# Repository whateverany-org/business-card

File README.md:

# business-card
My first ever PCB, a clone of https://www.thirtythreeforty.net/posts/2019/12/my-business-card-runs-linux. Completely untested, so not sure if it works or not. Build is waiting on on development of my reflow oven https://github.com/whateverany-org/reflow-oven.

# pcbdraw

## setup env
Create local env secrets and OCI container(s)
```
cp .env.template .env
vi .env
make oci-secrets
# rerun make oci-secrets if any changes to .env
make build
```

## create pcbdraw
```
make pcbdraw
```

### python venv hax
```
      
python3 -m venv .venv

```
rm -rf .venv/
python3 -m venv --system-site-packages .venv
source .venv/bin/activate
```

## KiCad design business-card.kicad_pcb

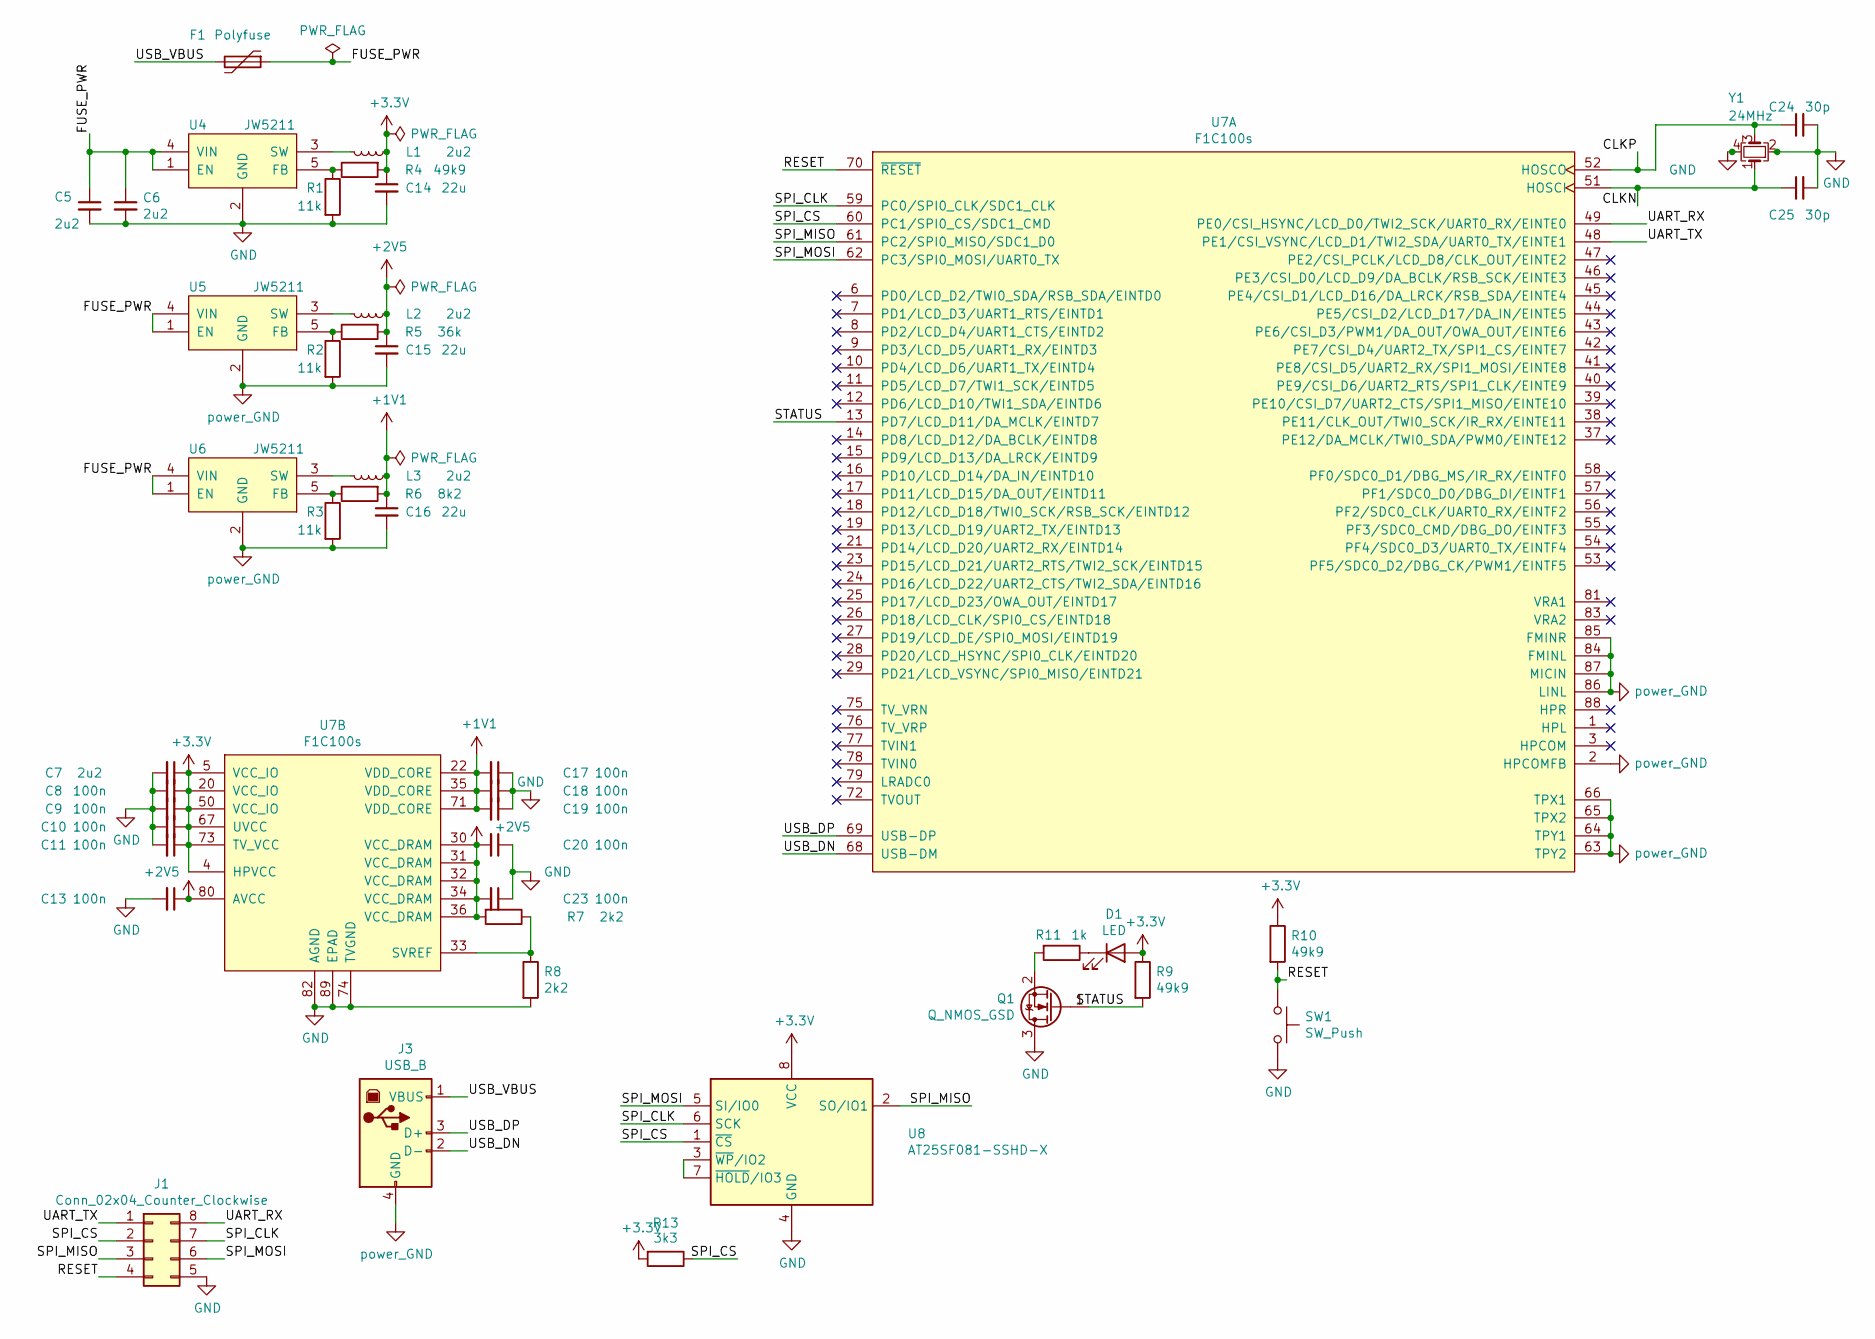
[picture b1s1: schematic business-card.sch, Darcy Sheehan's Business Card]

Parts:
C5, C6: 2u2; C_0805_2012Metric_Pad1.15x1.40mm_HandSolder
C7: 2u2; C_0805_2012Metric_Pad1.18x1.45mm_HandSolder
C8, C9, C10, C11, C13, C17, C18, C19, C20, C23: 100n; C_0805_2012Metric_Pad1.15x1.40mm_HandSolder
C14, C15, C16: 22u; C_0805_2012Metric_Pad1.15x1.40mm_HandSolder
C24, C25: 30p; C_0805_2012Metric_Pad1.15x1.40mm_HandSolder
D1: LED; LED_0805_2012Metric_Pad1.15x1.40mm_HandSolder
F1: Polyfuse; Fuse_0805_2012Metric
J1: Conn_02x04_Counter_Clockwise; SOIC_clipProgSmall
J3: USB_B; usb-PCB
L1, L2, L3: 2u2; L_0805_2012Metric_Pad1.15x1.40mm_HandSolder
Q1: Q_NMOS_GSD; SOT-23
R1, R2, R3: 11k; R_0805_2012Metric_Pad1.15x1.40mm_HandSolder
R4, R9, R10: 49k9; R_0805_2012Metric_Pad1.15x1.40mm_HandSolder
R5: 36k; R_0805_2012Metric_Pad1.15x1.40mm_HandSolder
R6: 8k2; R_0805_2012Metric_Pad1.15x1.40mm_HandSolder
R7, R8: 2k2; R_0805_2012Metric_Pad1.15x1.40mm_HandSolder
R11: 1k; R_0805_2012Metric_Pad1.15x1.40mm_HandSolder
R13: 3k3; R_0805_2012Metric_Pad1.15x1.40mm_HandSolder
SW1: SW_Push; SW_SPST_FSMSM
U4, U5, U6: JW5211; SOT-23-5
U7: F1C100s; QFN-88_EP_10x10_Pitch0.4mm
U8: AT25SF081-SSHD-X; SOIC-8_3.9x4.9mm_P1.27mm
Y1: 24MHz; Oscillator_SMD_Abracon_ASE-4Pin_3.2x2.5mm

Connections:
+1V1: C16.1, C17.2, C18.2, C19.2, L3.1, R6.2, U7.22 (VDD_CORE), U7.35 (VDD_CORE), U7.71 (VDD_CORE)
+2V5: C13.1, C15.1, C20.2, C23.2, L2.1, R5.2, R7.2, U7.30 (VCC_DRAM), U7.31 (VCC_DRAM), U7.32 (VCC_DRAM), U7.34 (VCC_DRAM), U7.36 (VCC_DRAM), U7.80 (AVCC)
+3V3: C7.1, C8.1, C9.1, C10.1, C11.1, C14.1, D1.2 (A), L1.1, R4.2, R9.1, R10.1, R13.2, U7.4 (HPVCC), U7.5 (VCC_IO), U7.20 (VCC_IO), U7.50 (VCC_IO), U7.67 (UVCC), U7.73 (TV_VCC), U8.8 (VCC)
/CLKN: C25.1, U7.51 (HOSCI), Y1.1
/CLKP: C24.1, U7.52 (HOSCO), Y1.3
/FUSE_PWR: C5.1, C6.1, F1.1, U4.1 (EN), U4.4 (VIN), U5.1 (EN), U5.4 (VIN), U6.1 (EN), U6.4 (VIN)
/RESET: J1.4, R10.2, SW1.1, U7.70 (~RESET)
/SPI_CLK: J1.7, U7.59 (PC0/SPI0_CLK/SDC1_CLK), U8.6 (SCK)
/SPI_CS: J1.2, R13.1, U7.60 (PC1/SPI0_CS/SDC1_CMD), U8.1 (~CS)
/SPI_MISO: J1.3, U7.61 (PC2/SPI0_MISO/SDC1_D0), U8.2 (SO/IO1)
/SPI_MOSI: J1.6, U7.62 (PC3/SPI0_MOSI/UART0_TX), U8.5 (SI/IO0)
/STATUS: Q1.1 (G), R9.2, U7.13 (PD7/LCD_D11/DA_MCLK/EINTD7)
/UART_RX: J1.8, U7.49 (PE0/CSI_HSYNC/LCD_D0/TWI2_SCK/UART0_RX/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)
/UART_TX: J1.1, U7.48 (PE1/CSI_VSYNC/LCD_D1/TWI2_SDA/UART0_TX/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)
/USB_DN: J3.2 (D-), U7.68 (USB-DM)
/USB_DP: J3.3 (D+), U7.69 (USB-DP)
/USB_VBUS: F1.2, J3.1 (VBUS)
unnamed: D1.1 (K), R11.1
unnamed: L1.2, U4.3 (SW)
unnamed: L2.2, U5.3 (SW)
unnamed: L3.2, U6.3 (SW)
unnamed: Q1.2 (S), R11.2
unnamed: R1.1, R4.1, U4.5 (FB)
unnamed: R2.1, R5.1, U5.5 (FB)
unnamed: R3.1, R6.1, U6.5 (FB)
unnamed: R7.1, R8.1, U7.33 (SVREF)
unnamed: U8.3 (~WP~/IO2), U8.7 (~HOLD~/IO3)

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
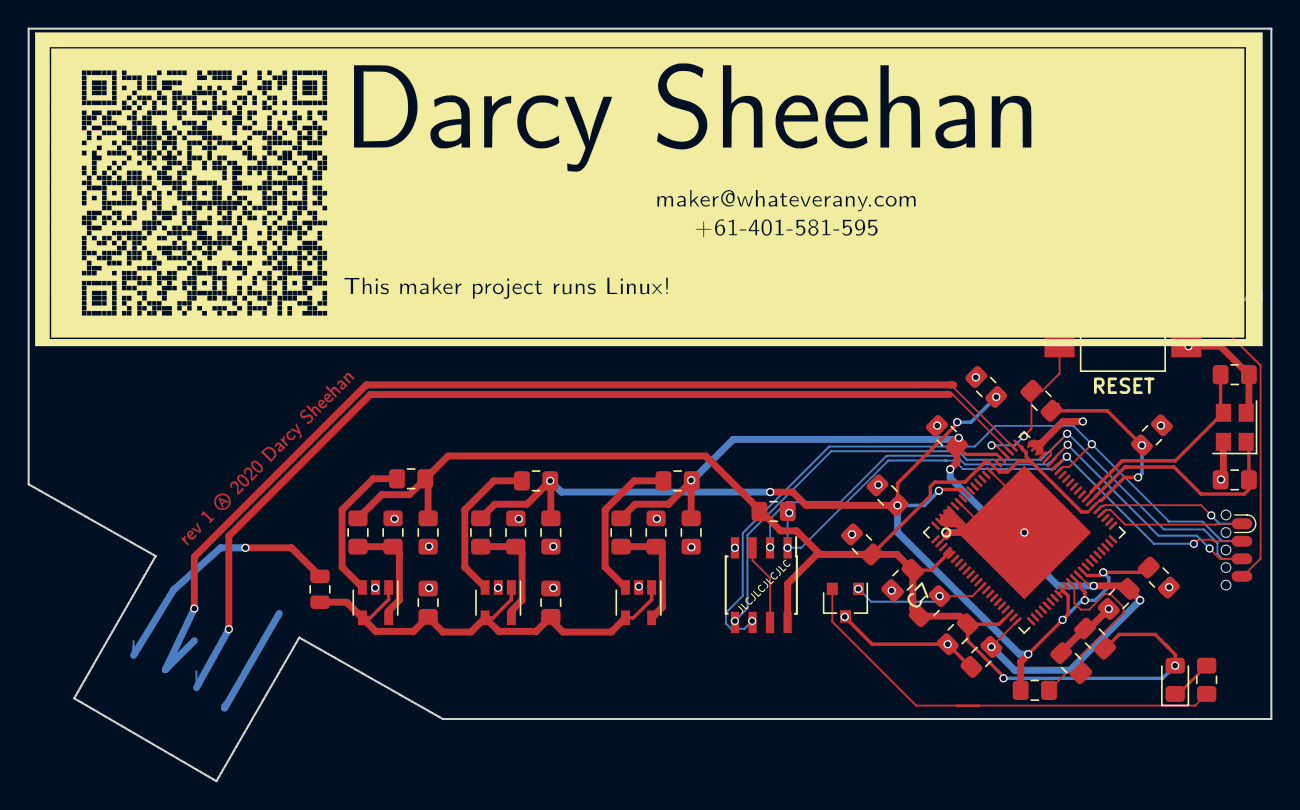
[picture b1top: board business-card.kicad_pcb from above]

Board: 2 copper layers, 90.0 x 54.5 mm, 45 parts (1 on the bottom side), 28 nets.

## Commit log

2020-11-29 stage 1
2020-11-30 Remove traces to try autoroute
2020-11-30 cleanup
2020-12-03 Complete board.
2020-12-06 images.
2020-12-10 rev 1
2020-12-10 rev1 update
2020-12-11 Added B.Mask layer to project.
2025-10-17 reorg

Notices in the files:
business-card.sch:
Copyleft ()) 2020 Darcy Sheehan
